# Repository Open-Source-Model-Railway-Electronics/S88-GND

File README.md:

# OS-S88n-GND

## 📄 Documentation

- [View the Manual (PDF, shared with CS version)](https://github.com/Open-Source-Model-Railway-Electronics/S88-CS/blob/main/docs/Manual.pdf)

## 🖼️ Hardware Preview

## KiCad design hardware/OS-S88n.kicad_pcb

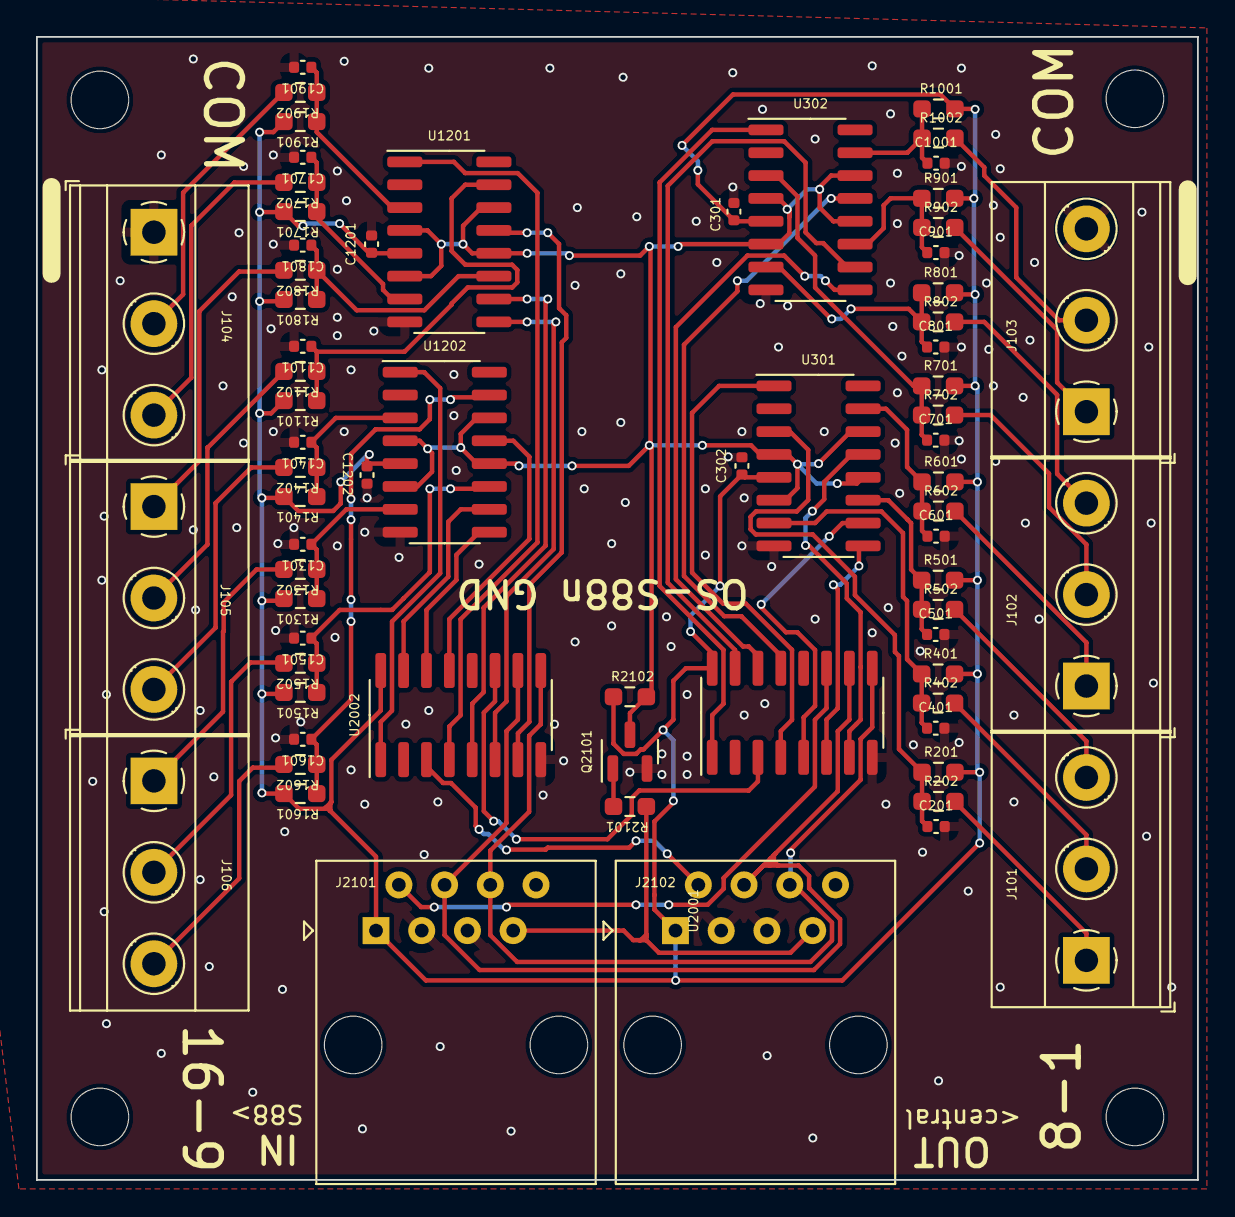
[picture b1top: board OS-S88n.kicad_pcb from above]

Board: 2 copper layers, 64.5 x 63.5 mm, 69 parts (0 on the bottom side), 57 nets.

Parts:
C201, C301, C302, C401, C501, C601, C701, C801, C901, C1001, C1101, C1201, C1202, C1301, C1401, C1501, C1601, C1701, C1801, C1901: 100nF; C_0402_1005Metric
J101, J102, J103, J104, J105, J106: Screw_Terminal_01x03; TerminalBlock_Phoenix_MKDS-1,5-3-5.08_1x03_P5.08mm_Horizont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
J2101, J2102: RJ45; RJ45_Amphenol_54602-x08_Horizontal
Q2101: BC847; SOT-23
R201, R401, R501, R601, R701, R801, R901, R1001, R1101, R1301, R1401, R1501, R1601, R1701, R1801, R1901, R2102: 100k; R_0603_smalltext
R202, R402, R502, R602, R702, R802, R902, R1002, R1102, R1302, R1402, R1502, R1602, R1702, R1802, R1902: 10k; R_0603_smalltext
R2101: 4k7; R_0603_smalltext
U301, U302, U1201, U1202: SOIC-16_3.9x9.9mm_P1.27mm
U2001, U2002: 4014; SOIC-16_3.9x9.9mm_P1.27mm

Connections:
/CS1/CMOS: C201.1, R201.1, R202.1, U301.3 (S1)
/CS1/TRACK: J101.1, R202.2
/CS2/CMOS: C401.1, R401.1, R402.1, U301.7 (S2)
/CS2/TRACK: J101.2, R402.2
/CS3/CMOS: C501.1, R501.1, R502.1, U301.11 (S3)
/CS3/TRACK: J101.3, R502.2
/CS4/CMOS: C601.1, R601.1, R602.1, U301.15 (S4)
/CS4/TRACK: J102.1, R602.2
/CS5/CMOS: C701.1, R701.1, R702.1, U302.3 (S1)
/CS5/TRACK: J102.2, R702.2
/CS6/CMOS: C801.1, R801.1, R802.1, U302.7 (S2)
/CS6/TRACK: J102.3, R802.2
/CS7/CMOS: C901.1, R901.1, R902.1, U302.11 (S3)
/CS7/TRACK: J103.1, R902.2
/CS8/CMOS: C1001.1, R1001.1, R1002.1, U302.15 (S4)
/CS8/TRACK: J103.2, R1002.2
/CS9/CMOS: C1901.1, R1901.1, R1902.1, U1201.3 (S1)
/CS9/TRACK: J104.2, R1902.2
/CS10/CMOS: C1701.1, R1701.1, R1702.1, U1201.7 (S2)
/CS10/TRACK: J104.3, R1702.2
/CS11/CMOS: C1801.1, R1801.1, R1802.1, U1201.11 (S3)
/CS11/TRACK: J105.1, R1802.2
/CS12/CMOS: C1101.1, R1101.1, R1102.1, U1201.15 (S4)
/CS12/TRACK: J105.2, R1102.2
/CS13/CMOS: C1401.1, R1401.1, R1402.1, U1202.3 (S1)
/CS13/TRACK: J105.3, R1402.2
/CS14/CMOS: C1301.1, R1301.1, R1302.1, U1202.7 (S2)
/CS14/TRACK: J106.1, R1302.2
/CS15/CMOS: C1501.1, R1501.1, R1502.1, U1202.11 (S3)
/CS15/TRACK: J106.2, R1502.2
/CS16/CMOS: C1601.1, R1601.1, R1602.1, U1202.15 (S4)
/CS16/TRACK: J106.3, R1602.2
/RJ45/CLOCK: J2101.4, U2001.10 (CP), U2002.10 (CP)
/RJ45/DATA_IN: J2101.2, U2001.11 (DS)
/RJ45/PL: J2101.6, U2001.9 (PL), U2002.9 (PL)
/RJ45/RESET: Q2101.3 (C), R2102.2, U301.4 (R1), U301.6 (R2), U301.12 (R3), U301.14 (R4), U302.4 (R1), U302.6 (R2), U302.12 (R3), U302.14 (R4), U1201.4 (R1), U1201.6 (R2), U1201.12 (R3), U1201.14 (R4), U1202.4 (R1), U1202.6 (R2), U1202.12 (R3), U1202.14 (R4)
/SR-latch1/Q1: U301.13 (Q1), U2001.7 (P0)
/SR-latch1/Q2: U301.9 (Q2), U2001.6 (P1)
/SR-latch1/Q3: U301.10 (Q3), U2001.5 (P2)
/SR-latch1/Q4: U301.1 (Q4), U2001.4 (P3)
/SR-latch1/Q5: U302.13 (Q1), U2001.13 (P4)
/SR-latch1/Q6: U302.9 (Q2), U2001.14 (P5)
/SR-latch1/Q7: U302.10 (Q3), U2001.15 (P6)
/SR-latch1/Q8: U302.1 (Q4), U2001.1 (P7)
/SR-latch2/Q1: U1201.13 (Q1), U2002.7 (P0)
/SR-latch2/Q2: U1201.9 (Q2), U2002.6 (P1)
/SR-latch2/Q3: U1201.10 (Q3), U2002.5 (P2)
/SR-latch2/Q4: U1201.1 (Q4), U2002.4 (P3)
/SR-latch2/Q5: U1202.13 (Q1), U2002.13 (P4)
/SR-latch2/Q6: U1202.9 (Q2), U2002.14 (P5)
/SR-latch2/Q7: U1202.10 (Q3), U2002.15 (P6)
/SR-latch2/Q8: U1202.1 (Q4), U2002.1 (P7)
GND: C201.2, C301.2, C302.2, C401.2, C501.2, C601.2, C701.2, C801.2, C901.2, C1001.2, C1101.2, C1201.2, C1202.2, C1301.2, C1401.2, C1501.2, C1601.2, C1701.2, C1801.2, C1901.2, J103.3, J104.1, J2101.3, J2101.5, Q2101.2 (E), U301.8 (GND), U302.8 (GND), U1201.8 (GND), U1202.8 (GND), U2001.8 (Vss), U2002.8 (Vss)
unnamed: J2101.7, R2101.1
unnamed: Q2101.1 (B), R2101.2
unnamed: U2001.3 (Q7), U2002.11 (DS)
VCC: C301.1, C302.1, C1201.1, C1202.1, J2101.1, R201.2, R401.2, R501.2, R601.2, R701.2, R801.2, R901.2, R1001.2, R1101.2, R1301.2, R1401.2, R1501.2, R1601.2, R1701.2, R1801.2, R1901.2, R2102.1, U301.5 (enable), U302.5 (enable), U1201.5 (enable), U1202.5 (enable), U2001.16 (Vdd), U2002.16 (Vdd)

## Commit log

2025-06-13 added initial files
2025-06-14 made release files
2025-06-17 added or renamed PNG preview
2025-06-19 Toegevoegd: handleiding (manual.odt)
2025-06-19 Hersteld: handleiding toegevoegd in docs/
2025-06-23 Added 3d files to the board, and made up the readme with manual and picture
2025-06-23 Updated png with the RJ45 connectors present.
